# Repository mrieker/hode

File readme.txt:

HODE 16-BIT TRANSISTOR COMPUTER

Website:  https://www.outerworldapps.com/hode

Uses a RaspberryPi for memory and IO (not needed for simulator).
Requires a Linux computer (x86 or raspi) to build software.
KiCad used to do PCB layouts.
Must have GNU C++ compiler, Java 8 or better dev kit.

Directories:

    asm      - cross assembler and linker
                $ make

    cc       - cross compiler
                $ make

    crtl     - C runtime library and example programs
                # make asm, cc, driver first
                $ cd library
                $ make
                $ cd ..
                $ make
                $ ./runit.sh circus.hex < test01.circ   ## runs in simlator (x86 or arm, no hode hardware required)
                $ ./runhw.sh circus.hex < test01.circ   ## runs on hode hardware that this raspi is plugged into

    de0      - DE0-Nano FPGA implementation (in verilog)
               requires de0-nano board, raspberry pi, kicads/de0raspi interconnect board
               use quartus to compile verilog in the de0 directory and program the de0-nano
               populate interconnect board with two 2x20 connectors and 26 33-ohm resistors
               plug raspi into the raspi connector and de0-nano gpio 1 into the de0 connector
               should be able to run any hode programs such as:

                # desktop calculator
                $ cd crtl
                $ ./runhw.sh calc.hex

                # rolling lights
                $ cd driver
                $ ./raspictl rollights.hex

    driver   - raspi control program and hardware test programs
                $ make
                $ cd km
                $ make                      ## on raspi only
                $ sudo insmod enabtsc.ko    ## on raspi only

                    note:  hexfile.hex is a placeholder for an actual hex file (see crtl directory)

                $ ./raspictl.armv7l       hexfile.hex   ## runs hexfile.hex on attached hode hardware
                                                        ## runs until hexfile.hex program calls exit()

                $ ./raspictl.armv7l -nohw hexfile.hex   ## simulator (no hode hardware required)

                $ ./raspictl.x86_64 -nohw hexfile.hex   ## simulator running on x86

    freecads - case component drawings

    goodpcbs - good pcb files (routing completed, including netlist and parts list files)

    kicads   - other kicad files
                de0raspi - interconnect for de0 nano and raspberry pi
                IOW56Paddle - IO-Warrior-56 paddles for board-level testing
                PowerDist - power distribution board - connects edge power to power supply

    modules  - board modules (verilog-like code)
                # make netgen first
                $ ./testmaster.sh   ## runs regression test scripts
                $ ./pcball.sh       ## generate raw .pcb files, need trace routing via kicad

    netgen   - java program to compile modules for simulation and pcb generation
                # make sure jninc_x86_64 or jninc_armv7l points to directory where jni.h is located
                $ make

For those makefiles that create objects and executables, they will create two versions,
one for x86_64 and one for armv7l, depending on which computer type they are run on.
Typically this is just done for the driver directory, once on a PC (creating the .x86_64
files) and once on a raspi (creating the .armv7l files).  The other directories are
typically only done on the PC but can be done on a raspi (either instead of or as well as).

HOW TO BUILD

    Each board takes a little under 1.5A at 5V * 9 boards = 13.5A + raspi (2.5A) = 16A.
    Get 40 2x20 stackable connectors (and a couple extra).
    Get 9 1x6 pin right angle connectors for power.

    Make the 4 paddles by making the circuit boards, populate with 10K 1/8 watt resistors,
    and get an IOWarrior-56 module for each.  Put a 2x20 stackable connector on each.
    Run drivers/iow56list.armv7l on the raspi to get the serial number for each one at a time.
    Label them A, C, I, D with little stickers and put the serial numbers in netgen/iow56sns.si.

    When populating the main boards, start with the diodes as they are uniquely marked.  Of course
    make sure the bands on the diodes match the bands on the board.  Next do the 2.7K resistors as
    they are among the diodes.  Next come the 680 resistors, they go near the transistor collector
    leads and then the 1K resistors that go near the transistor emitter leads.  Then do the bypass
    capacitors that go next to the transistor collector and emitter leads.  Finally put in the
    transistors then the edge connectors.

    When soldering the 2x20 stackable connectors to the boards, make sure they are mounted tightly
    on the boards so they will mate up when stacking the boards.  Be very careful when pulling the
    boards apart that you do not bend the pins on the stackable connectors.  Rock them little by
    little until each one comes apart.

    Optionally make an ledboard.pcb and populate.  It can be used for diagnostics as it shows the
    state of the bus connector pins.  It can be plugged into the other boards one at a time or in
    any combination.  It is not required for testing as the testing is all done via the paddles, but
    can make it easier to track down any problems.  Be careful to note 3 positions are populated
    with 2N3906s instead of the usual 2N3904s and the LEDs are reversed, as the _IR_WE, _PSW_IECLR,
    _PSW_REB signals are active low.

    Make a seqboard.pcb board and populate with diodes, resistors, capacitors, transistors, LEDs,
    connectors.  Connect to a variable power supply and turn slowly up to 5V, it should draw under
    1.5A.  Plug in the 4 paddles (actually just need C and I paddles).  Run the 'drivers/seqtester
    -cpuhz 200 -loop' script to test it.  The paddles are limited to 200Hz so that's why the '-cpuhz
    200' option is needed.

    Make a rasboard.pcb board and populate as usual.  You will also need a 2x20 connector for the
    raspi and a raspi 3 or 4 to plug into it.  The little 4x4 connector pins near the raspi connector
    jumpers the 5V power from the board's main power to the raspi.  With the jumpers removed, the
    raspi must be powered via its usual USB connector, otherwise the raspi will be powered from the
    board's 5V supply.  Once constructed, leave the raspi off the board and test it with a variable
    power supply like with the seqboard and see that it takes under 1.5A.  Then it should be ok to
    plug the raspi in.  You can use 7/16" spacers on 3/4" 4-40 screws to hold the raspi in place.
    Plug all 4 paddles into the edge of the rasboard and the USB cables into the raspi.  Run the
    'drivers/rastester.sh -cpuhz 200 -loop' script to test it.

    Plug the seqboard and rasboard together.  They should be oriented so the power connectors are at
    same position.  Run the 'drivers/raseqtest.sh -cpuhz 200 -loop' script to test it.  It assumes
    the 4 paddles are plugged in, if not, use the -nopads option on the command line and it will test
    as much as it can without it.  With -nopads, the two boards should run fast, so try leaving off the
    '-cpuhz 200' option.

    Make aluboards one at a time.  Jumper one as hi-byte and use 'drivers/alutester.sh -cpuhz 200 -loop
    hi' to test it with the 4 paddles.  Likewise make a lo-byte board and test it.

    Stack both aluboards and plug into the seqboard/rasboard stack.  Test with all 4 paddles plugged in
    to the stack and the raspi using the 'drivers/raseqtest.sh -alu -cpuhz 200 -loop' command.

    Finally come the register boards.  They can be tested individually with the 'drivers/regtester.sh 
    -cpuhz 200 -loop <nn>' script.  <nn> is 01, 23, 45, 67 depending on how the register board is
    jumpered.  When the board tests ok with the regtester script, it can be added to the seq/ras/alu
    stack and tested with 'drivers/raseqtest.sh -alu -cpuhz 200 -loop -reg<nn>' command.  Use a
    -reg01, -reg23, -reg45, -reg67 option for each register board you have put in the stack.

    When all 8 boards are completed, they can be tested at full speed with the 'drivers/raspictl.armv7l
    -randmem -mintimes' command.  It should run for days and days.  You can experiment with the -cpuhz
    option to specify different clocking frequencies.

    Then you can go to the crtl directory and run a program with the ./runhw.sh script, such as
    './runhw.sh printpi.hex' or './runhw.sh circus.hex < test01.circ'.

    Note that it doesn't matter what order the boards are stacked in, electrically speaking.  You can
    shuffle them around for testing and debugging.  But it is best to put the sequencer board on the
    front when you get it all working so you can see the blinking state LEDs.  If you make the optional
    LED board, it goes in front of the sequencer board and does not block any of the sequencer board's
    LEDs.

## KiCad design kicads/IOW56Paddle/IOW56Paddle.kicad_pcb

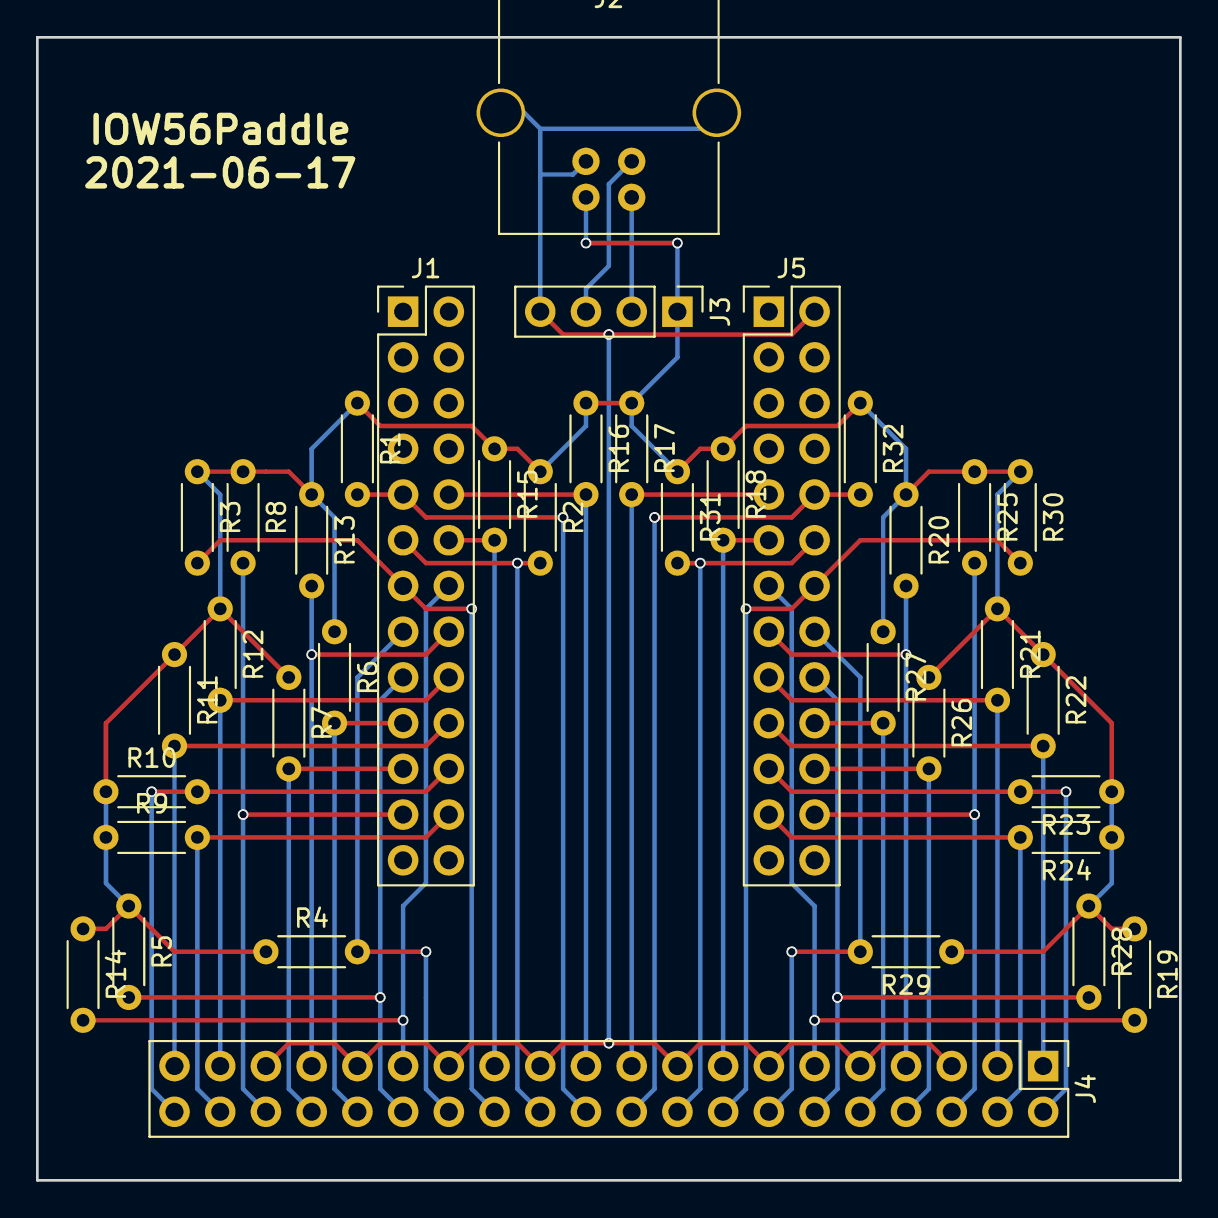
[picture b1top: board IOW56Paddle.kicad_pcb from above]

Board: 2 copper layers, 63.5 x 63.5 mm, 37 parts (0 on the bottom side), 36 nets.

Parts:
J1, J5: CONN_02X13; Pin_Header_Straight_2x13_Pitch2.54mm
J2: USB_B
J3: CONN_01X04; Pin_Header_Straight_1x04_Pitch2.54mm
J4: CONN_02X20; Pin_Header_Straight_2x20_Pitch2.54mm
R1, R2, R3, R4, R5, R6, R7, R8, R9, R10, R11, R12, R13, R14, R15, R16, R17, R18, R19, R20, R21, R22, R23, R24, R25, R26, R27, R28, R29, R30, R31, R32: R; R_Axial_DIN0204_L3.6mm_D1.6mm_P5.08mm_Horizontal

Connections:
GND: J2.4, J2.5, J3.4, J4.5, J4.9, J4.13, J4.17, J4.23, J4.27, J4.31, J4.35, J5.2
unnamed: J1.9, J4.22, R1.2
unnamed: J1.10, J4.21, R16.2
unnamed: J1.11, J4.24, R2.2
unnamed: J1.12, J4.25, R15.2
unnamed: J1.13, J4.26, R3.2
unnamed: J1.14, J4.29, R14.2
unnamed: J1.15, J4.28, R4.2
unnamed: J1.16, J4.33, R13.2
unnamed: J1.17, J4.30, R5.2
unnamed: J1.18, J4.37, R12.2
unnamed: J1.19, J4.32, R6.2
unnamed: J1.20, J4.39, R11.2
unnamed: J1.21, J4.34, R7.2
unnamed: J1.22, J4.40, R10.2
unnamed: J1.23, J4.36, R8.2
unnamed: J1.24, J4.38, R9.2
unnamed: J2.1, J3.1, R1.1, R2.1, R3.1, R4.1, R5.1, R6.1, R7.1, R8.1, R9.1, R10.1, R11.1, R12.1, R13.1, R14.1, R15.1, R16.1, R17.1, R18.1, R19.1, R20.1, R21.1, R22.1, R23.1, R24.1, R25.1, R26.1, R27.1, R28.1, R29.1, R30.1, R31.1, R32.1
unnamed: J2.2, J3.2
unnamed: J2.3, J3.3
unnamed: J4.1, J5.19, R22.2
unnamed: J4.2, J5.21, R23.2
unnamed: J4.3, J5.17, R21.2
unnamed: J4.4, J5.23, R24.2
unnamed: J4.6, J5.24, R25.2
unnamed: J4.7, J5.15, R20.2
unnamed: J4.8, J5.22, R26.2
unnamed: J4.10, J5.20, R27.2
unnamed: J4.11, J5.13, R19.2
unnamed: J4.12, J5.18, R28.2
unnamed: J4.14, J5.16, R29.2
unnamed: J4.15, J5.11, R18.2
unnamed: J4.16, J5.14, R30.2
unnamed: J4.18, J5.12, R31.2
unnamed: J4.19, J5.9, R17.2
unnamed: J4.20, J5.10, R32.2

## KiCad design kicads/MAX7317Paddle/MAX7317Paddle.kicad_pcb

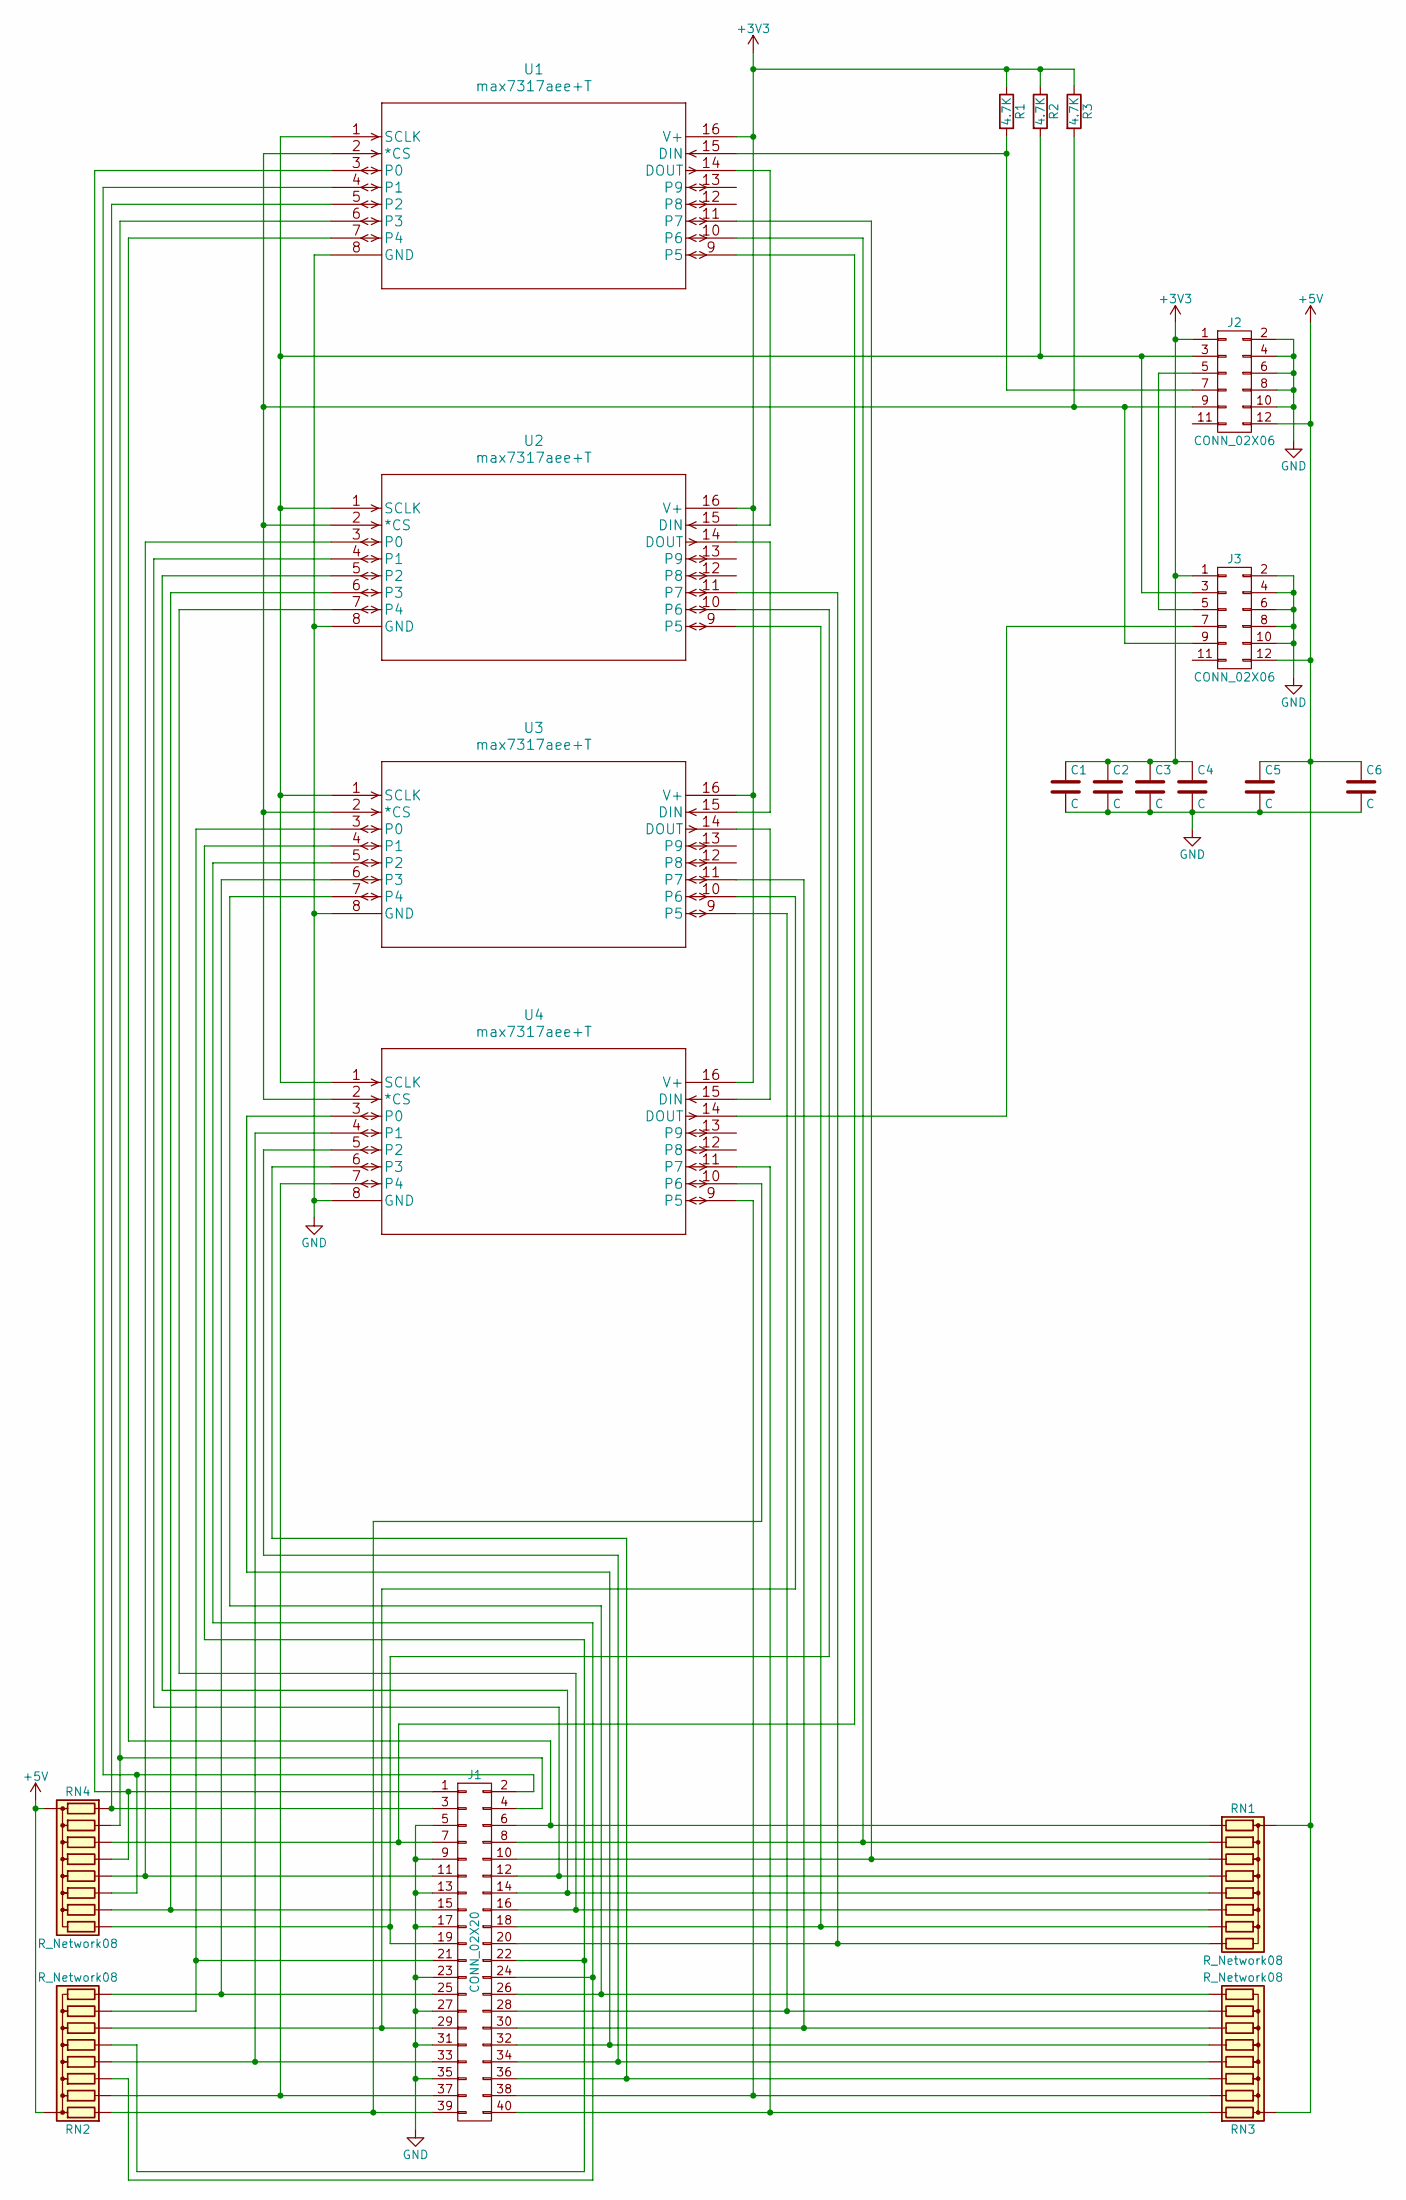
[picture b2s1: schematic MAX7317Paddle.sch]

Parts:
C1, C2, C3, C4: C; C_Rect_L7.0mm_W2.5mm_P5.00mm
C5, C6: C; C_Axial_L5.1mm_D3.1mm_P7.50mm_Horizontal
J1: CONN_02X20; Pin_Header_Straight_2x20_Pitch2.54mm
J2, J3: CONN_02X06; Pin_Header_Straight_2x06_Pitch2.54mm
R1, R2, R3: 4.7K; R_Axial_DIN0204_L3.6mm_D1.6mm_P5.08mm_Horizontal
RN1, RN2, RN3, RN4: R_Network08; R_Array_SIP9
U1, U2, U3, U4: max7317aee+T; max7317aee&plus_T

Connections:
+3V3: C1.1, C2.1, C3.1, C4.1, J2.1, J3.1, R1.1, R2.1, R3.1, U1.16 (V+), U2.16 (V+), U3.16 (V+), U4.16 (V+)
+5V: C5.1, C6.1, J2.12, J3.12, RN1.1 (common), RN2.1 (common), RN3.1 (common), RN4.1 (common)
GND: C1.2, C2.2, C3.2, C4.2, C5.2, C6.2, J1.5, J1.9, J1.13, J1.17, J1.23, J1.27, J1.31, J1.35, J2.2, J2.4, J2.6, J2.8, J2.10, J3.2, J3.4, J3.6, J3.8, J3.10, U1.8 (GND), U2.8 (GND), U3.8 (GND), U4.8 (GND)
unnamed: J1.1, RN4.5 (R4), U1.3 (P0)
unnamed: J1.2, RN4.7 (R6), U1.4 (P1)
unnamed: J1.3, RN4.2 (R1), U1.5 (P2)
unnamed: J1.4, RN4.3 (R2), U1.6 (P3)
unnamed: J1.6, RN1.2 (R1), U1.7 (P4)
unnamed: J1.7, RN4.4 (R3), U1.9 (P5)
unnamed: J1.8, RN1.3 (R2), U1.10 (P6)
unnamed: J1.10, RN1.4 (R3), U1.11 (P7)
unnamed: J1.11, RN4.6 (R5), U2.3 (P0)
unnamed: J1.12, RN1.5 (R4), U2.4 (P1)
unnamed: J1.14, RN1.6 (R5), U2.5 (P2)
unnamed: J1.15, RN4.8 (R7), U2.6 (P3)
unnamed: J1.16, RN1.7 (R6), U2.7 (P4)
unnamed: J1.18, RN1.8 (R7), U2.9 (P5)
unnamed: J1.19, RN4.9 (R8), U2.10 (P6)
unnamed: J1.20, RN1.9 (R8), U2.11 (P7)
unnamed: J1.21, RN2.8 (R7), U3.3 (P0)
unnamed: J1.22, RN2.6 (R5), U3.4 (P1)
unnamed: J1.24, RN2.4 (R3), U3.5 (P2)
unnamed: J1.25, RN2.9 (R8), U3.6 (P3)
unnamed: J1.26, RN3.9 (R8), U3.7 (P4)
unnamed: J1.28, RN3.8 (R7), U3.9 (P5)
unnamed: J1.29, RN2.7 (R6), U3.10 (P6)
unnamed: J1.30, RN3.7 (R6), U3.11 (P7)
unnamed: J1.32, RN3.6 (R5), U4.3 (P0)
unnamed: J1.33, RN2.5 (R4), U4.4 (P1)
unnamed: J1.34, RN3.5 (R4), U4.5 (P2)
unnamed: J1.36, RN3.4 (R3), U4.6 (P3)
unnamed: J1.37, RN2.3 (R2), U4.7 (P4)
unnamed: J1.38, RN3.3 (R2), U4.9 (P5)
unnamed: J1.39, RN2.2 (R1), U4.10 (P6)
unnamed: J1.40, RN3.2 (R1), U4.11 (P7)
unnamed: J2.3, J3.3, R2.2, U1.1 (SCLK), U2.1 (SCLK), U3.1 (SCLK), U4.1 (SCLK)
unnamed: J2.5, J3.5
unnamed: J2.7, R1.2, U1.15 (DIN)
unnamed: J2.9, J3.9, R3.2, U1.2 (*CS), U2.2 (*CS), U3.2 (*CS), U4.2 (*CS)
unnamed: J3.7, U4.14 (DOUT)
unnamed: U1.14 (DOUT), U2.15 (DIN)
unnamed: U2.14 (DOUT), U3.15 (DIN)
unnamed: U3.14 (DOUT), U4.15 (DIN)

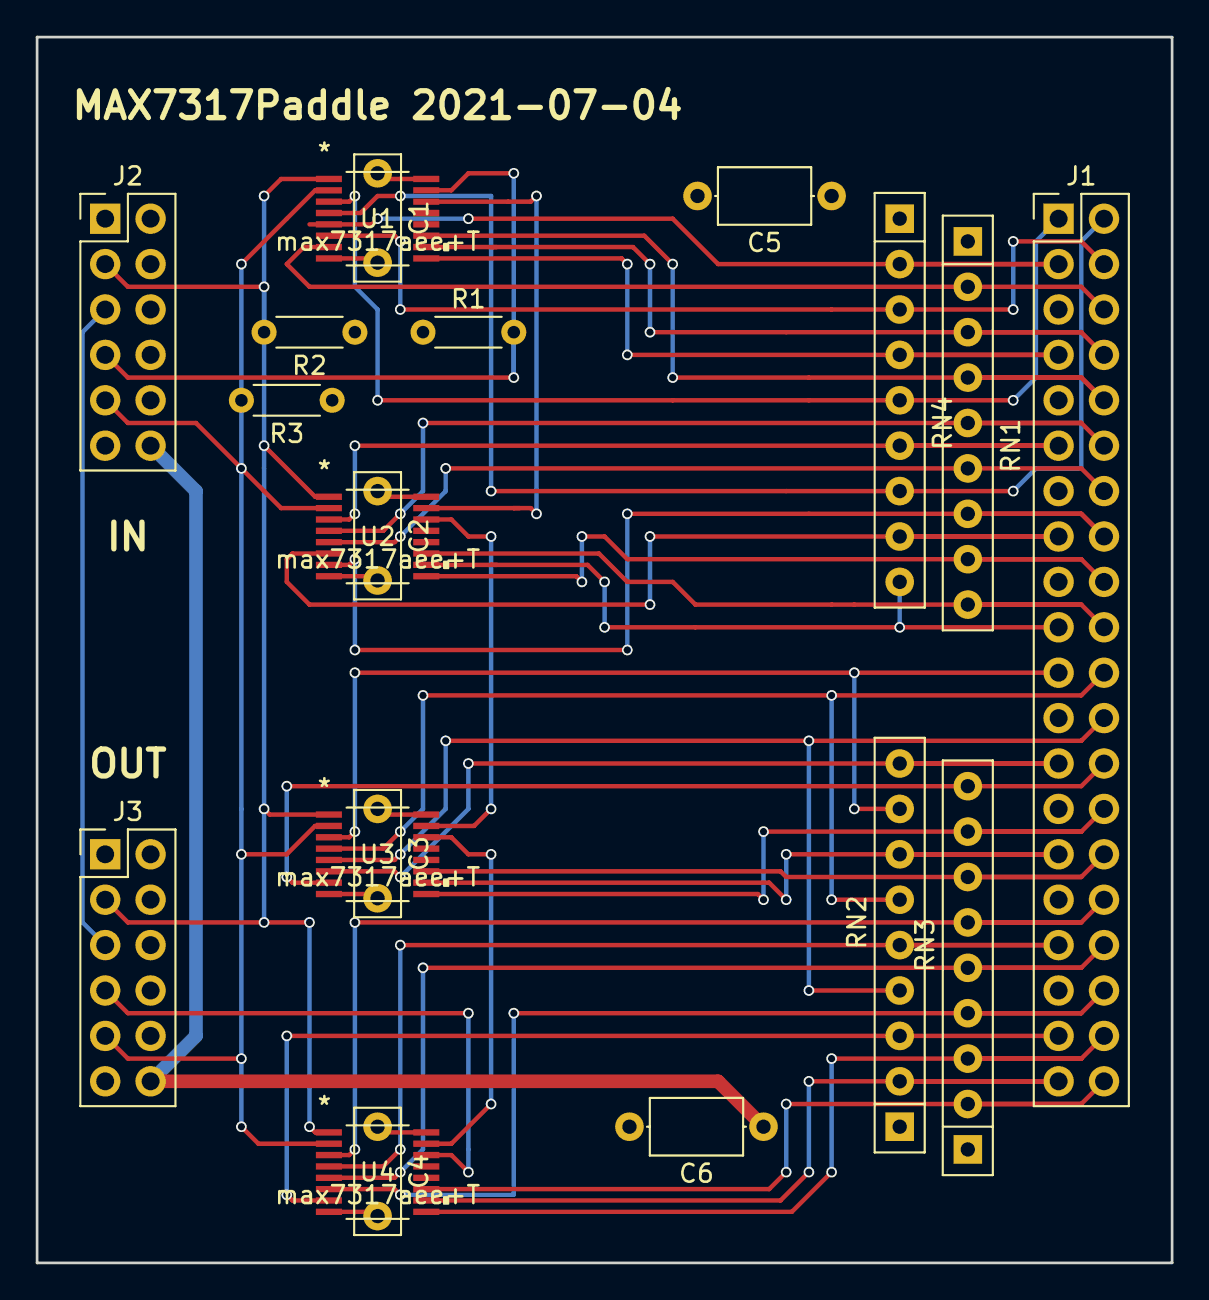
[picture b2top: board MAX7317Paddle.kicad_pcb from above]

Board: 4 copper layers, 63.5 x 68.6 mm, 20 parts (0 on the bottom side), 43 nets.

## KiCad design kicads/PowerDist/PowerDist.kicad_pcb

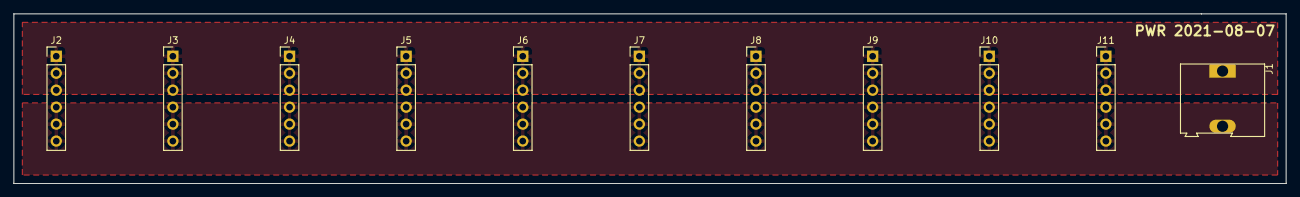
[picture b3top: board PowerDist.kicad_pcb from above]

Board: 2 copper layers, 190.5 x 25.4 mm, 11 parts (0 on the bottom side), 2 nets, no tracks yet.

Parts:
J1: Screw_Terminal_1x02; AK300-2
J2, J3, J4, J5, J6, J7, J8, J9, J10, J11: CONN_01X06; Pin_Header_Straight_1x06_Pitch2.54mm

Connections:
GND: J1.2, J2.4, J2.5, J2.6, J3.4, J3.5, J3.6, J4.4, J4.5, J4.6, J5.4, J5.5, J5.6, J6.4, J6.5, J6.6, J7.4, J7.5, J7.6, J8.4, J8.5, J8.6, J9.4, J9.5, J9.6, J10.4, J10.5, J10.6, J11.4, J11.5, J11.6
VCC: J1.1, J2.1, J2.2, J2.3, J3.1, J3.2, J3.3, J4.1, J4.2, J4.3, J5.1, J5.2, J5.3, J6.1, J6.2, J6.3, J7.1, J7.2, J7.3, J8.1, J8.2, J8.3, J9.1, J9.2, J9.3, J10.1, J10.2, J10.3, J11.1, J11.2, J11.3

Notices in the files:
parts and their libraries:
Copyright 2021 Accelerated Designs. All rights reserved.
